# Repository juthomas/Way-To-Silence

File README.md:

# WAY TO SILENCE

## Goals
- Develop a module based on the ESP32, designed to read audio tracks stored on an SD card and to transmit them through a speaker output. Users should be able to adjust the parameters of these audio tracks, such as volume and balance, via an intuitive and easily accessible web interface. Furthermore, control over the tracks and playback settings via UDP signals is essential. This interface will provide users with the opportunity to customize their listening experience and adjust settings to their preferences. It will also ensure quick and efficient communication with the module through the UDP protocol. In addition, effective battery management is crucial to ensure the module's durability and optimal performance.

## 3D Render

## Schematics

- [Link to pdf](https://github.com/juthomas/Way-To-Silence/blob/main/Schematics%20PDF/Way%20to%20silence.pdf)

## Bill Of Materials

- [Link to IBOM](https://juthomas.github.io/Way-To-Silence/)
## Components
- [I2S Amplifier Module MAX98357A](https://www.lcsc.com/product-detail/Audio-Power-OpAmps_Analog-Devices-Inc-Maxim-Integrated-MAX98357AETE-T_C910544.html) € 0.7886

- [SD Card Connector](https://jlcpcb.com/partdetail/gswitch-GT_TF003_H018502/C5155564) € 0.1553

- [ESP32 4Mb Flash](https://www.lcsc.com/product-detail/WiFi-Modules_Espressif-Systems-ESP32-WROOM-32-N4_C82899.html) € 2.5764

- [ESP32 8Mb Flash](https://www.lcsc.com/product-detail/WiFi-Modules_Espressif-Systems-ESP32-WROOM-32-N8_C529582.html) € 2.9722

- [ESP32 16Mb Flash](https://lcsc.com/product-detail/WiFi-Modules_Espressif-Systems-ESP32-WROOM-32-N16_C529581.html) € 3.3920

- [CP2102](https://www.lcsc.com/product-detail/USB-ICs_SILICON-LABS-CP2102-GMR_C6568.html) € 2.0075

- [CH340C](https://www.lcsc.com/product-detail/USB-ICs_WCH-Jiangsu-Qin-Heng-CH340C_C84681.html) € 0.45

- [BMS SM5308](https://www.lcsc.com/product-detail/Battery-Management-ICs_HICHON-SM5308_C5345582.html) € 0.2758
- [USB C Connector](https://jlcpcb.com/partdetail/Dealon-USB_TYPE_C018/C2927038) $ 0.0479
- [3.3V Regulator](https://www.lcsc.com/product-detail/Linear-Voltage-Regulators-LDO_UMW-Youtai-Semiconductor-Co-Ltd-AMS1117-3-3_C347222.html) € 0.0398

- [Bornier 3.5mm](https://www.lcsc.com/product-detail/Screw-terminal_Ningbo-Xinlaiya-Elec-XY350V-3-5-2P_C784942.html) € 0.1065
- [2.2uH Inductance](https://www.lcsc.com/product-detail/Inductors-SMD_KOHERelec-MDA4020-2R2M_C2847469.html) € 0.7154
- [1uH Inductance](https://www.lcsc.com/product-detail/Inductors-SMD_KOHERelec-MDA4020-1R0M_C2847468.html#) € 0.7287
- [Battery Switch](https://jlcpcb.com/partdetail/XkbConnectivity-SS12D10L3/C319013) € 0.8814
- [Reset Button](https://jlcpcb.com/partdetail/Xunpu-TS_1088R02026/C455280) € 0.0448

- [4.7nF Capacitor](https://jlcpcb.com/partdetail/55004-0603B472K500NT/C53987) € 0.0025
- [4.7uF Capacitor](https://jlcpcb.com/partdetail/20375-CL10A475KO8NNNC/C19666) € 0.0095
- [10uF Capacitor](https://jlcpcb.com/partdetail/MurataElectronics-GRM188R60J106ME47D/C77041) € 0.0085	
- [22uF Capacitor](https://jlcpcb.com/partdetail/60514-CL10A226MQ8NRNC/C59461) € 0.0085
- [100nF Capacitor](https://jlcpcb.com/partdetail/Yageo-CC0603KRX7R9BB104/C14663) € 0.0022
- [220pF Capacitor](https://jlcpcb.com/partdetail/1955-CL10B221KB8NNNC/C1603) € 0.0055
- [0Ω Resistor](https://jlcpcb.com/partdetail/21903-0603WAF0000T5E/C21189) € 0.0011
- [100mΩ Resistor](https://jlcpcb.com/partdetail/112253-0603WAF100LT5E/C111027) € 0.0039
- [500mΩ Resistor](https://jlcpcb.com/partdetail/Fojan-FRL0603FR500TS/C2934253) € 0.0031
- [1Ω Resistor](https://jlcpcb.com/partdetail/25955-0603WAJ010JT5E/C25212) € 0.0009
- [1kΩ Resistor](https://jlcpcb.com/partdetail/21904-0603WAF1001T5E/C21190) € 0.0006

- [5.11kΩ Resistor](https://jlcpcb.com/partdetail/419038-TC0350B5111T5E/C425414) € 0.0167
- [10kΩ Resistor](https://jlcpcb.com/partdetail/26547-0603WAF1002T5E/C25804) € 0.0009
- [1MΩ Resistor](https://jlcpcb.com/partdetail/23662-0603WAF1004T5E/C22935) € 0.0011
- [Red LED](https://jlcpcb.com/partdetail/85432-NCD0603R1/C84263) € 0.0078
- [Yellow LED](https://jlcpcb.com/partdetail/85437-NCD0603Y1/C84268) € 0.0111
- [Ferrite Bead](https://jlcpcb.com/partdetail/373749-CBW160808U470T/C394474) € 0.0030
- [Transistor](https://jlcpcb.com/partdetail/Shikues-BC817/C475629) € 0.0150

## Tools used

- [KiCad](https://www.kicad.org/)
- [KiCad Fabrication Toolkit Plugin](https://github.com/bennymeg/JLC-Plugin-for-KiCad)
- [KiCad Interactive Html Bom Plugin](https://github.com/openscopeproject/InteractiveHtmlBom)
- [LCSC](https://www.lcsc.com/)
- [JCLPCB](https://jlcpcb.com/)

- [EasyEDA to KiCad](https://wokwi.com/tools/easyeda2kicad)

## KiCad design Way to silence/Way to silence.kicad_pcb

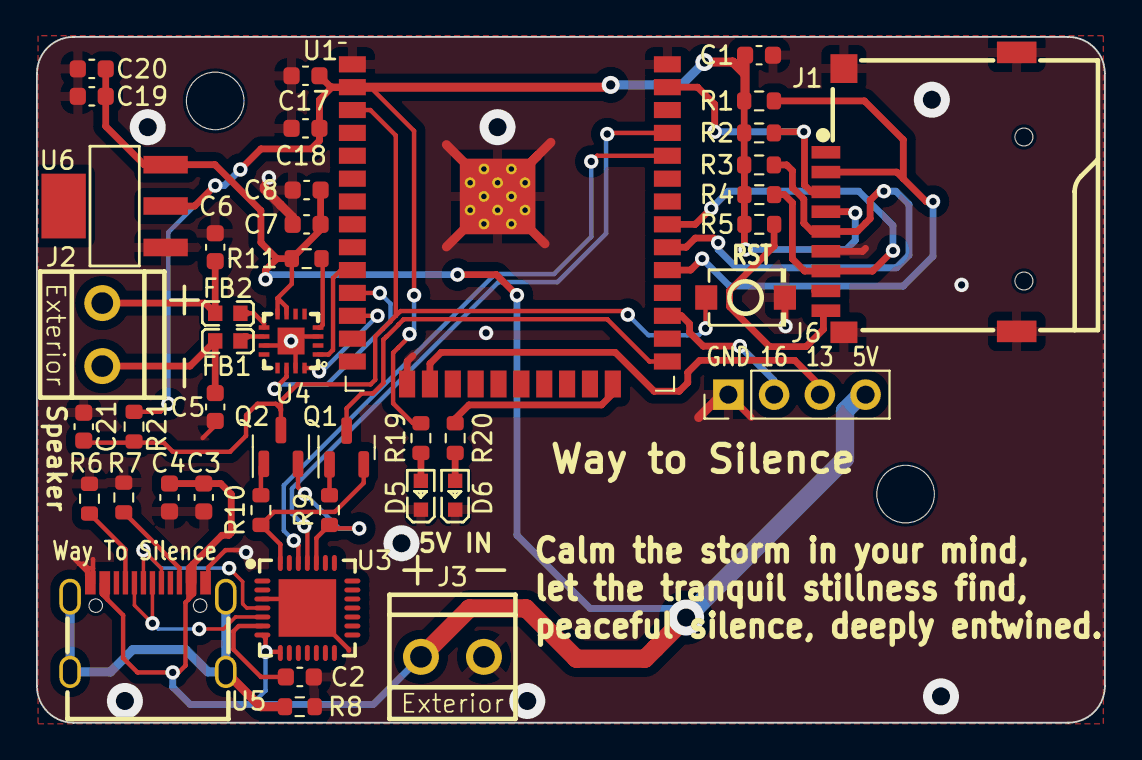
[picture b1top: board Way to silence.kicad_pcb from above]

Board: 2 copper layers, 59.3 x 38.1 mm, 45 parts (0 on the bottom side), 35 nets.

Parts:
C1, C2, C3, C7, C18, C19: 100nF; C_0603_1608Metric
C4: 4.7uF; C_0603_1608Metric
C5, C6: 220pF; C_0603_1608Metric
C8, C17, C20, C21: 10uF; C_0603_1608Metric
D5, D6: LED; LED_0603
FB1, FB2: FerriteBead; FB_0603
H1, H2: MountingHole; MountingHole_3.2mm_M3
J1: SD Card Connector; SD_Card_Connector
J2: Amplificator_Terminal; Screw_Terminal_3.5
J3: 5V_Terminal; Screw_Terminal_3.5
J6: Conn_01x04_Pin; PinHeader_1x04_P2.54mm_Vertical
Q1, Q2: BC817; SOT-23
R1, R2, R3, R4, R5, R9, R10, R21: 10K; R_0603_1608Metric
R6, R7: 5.11K; R_0603_1608Metric
R8, R11: 1M; R_0603_1608Metric
R19, R20: 1K; R_0603_1608Metric
SW3: SW_SPST
U1: ESP32-WROOM-32-N16; ESP32-WROOM-32
U3: CP2102-GMR; CP2102
U4: MAX98357AETE+T; MAX98357
U5: USB-TYPE-C-018; USB_C_Receptacle
U6: AMS1117CD-3.3

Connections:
+3.3V: C1.1, C17.2, C18.2, J1.4 (VDD), R1.1, R2.1, R3.1, R4.1, R5.1, R19.2, R21.1, U1.2 (VDD), U6.2 (VO)
+5V: C3.2, C4.2, C7.2, C8.2, C19.2, C20.2, J3.1, J6.4, R11.1, U3.7 (VREGIN), U3.8 (VBUS), U4.7 (VDD), U4.8 (VDD), U5.A4 (VBUS), U5.A9 (VBUS), U5.B4 (VBUS), U5.B9 (VBUS), U6.3 (VI)
/ESP_EN: C21.2, Q2.3 (C), R21.2, SW3.1 (A), U1.3 (EN)
/ESP_IO0: Q1.3 (C), U1.25 (IO0)
/ESP_IO2: R20.2, U1.24 (IO2)
/ESP_IO5: J1.2 (DAT3/CD), R1.2, U1.29 (IO5)
/ESP_IO13: J6.3, U1.16 (IO13)
/ESP_IO16: J6.2, U1.27 (IO16)
/ESP_IO18: J1.5 (CLK), R3.2, U1.30 (IO18)
/ESP_IO19: J1.7 (DAT0), R4.2, U1.31 (IO19)
/ESP_IO23: J1.3 (CMD), R2.2, U1.37 (IO23)
/ESP_IO25: U1.10 (IO25), U4.1 (DIN)
/ESP_IO26: U1.11 (IO26), U4.14 (LRCLK)
/ESP_IO27: U1.12 (IO27), U4.16 (BCLK)
/ESP_RX: U1.34 (RXD0/IO3), U3.26 (TXD)
/ESP_TX: U1.35 (TXD0/IO1), U3.25 (RXD)
/I2S Amp/SD: R11.2, U4.4 (SD_MODE)
/SD Card/Card Inserted: J1.CD (Card_Inserted), R5.2
/USB to Uart/DN: U3.5 (D-), U5.A7 (DN1), U5.B7 (DN2)
/USB to Uart/DP: U3.4 (D+), U5.A6 (DP1), U5.B6 (DP2)
/USB to Uart/SH: R8.1, U5.0 (SH), U5.1 (SH), U5.2 (SH), U5.3 (SH)
GND: C1.2, C2.1, C3.1, C4.1, C5.1, C6.1, C7.1, C8.1, C17.1, C18.1, C19.1, C20.1, C21.1, D5.1 (K), D6.1 (K), J1.6 (VSS), J1.G (SHIELD), J3.2, J6.1, R6.2, R7.1, R8.2, SW3.2 (B), U1.1 (GND), U1.15 (GND), U1.38 (GND), U1.39 (GND), U3.3 (GND), U3.29 (GND), U4.3 (GND), U4.11 (GND), U4.15 (GND), U4.17 (EP), U5.A1 (GND), U5.A12 (GND), U5.B1 (GND), U5.B12 (GND), U6.1 (GND)
unnamed: D5.2 (A), R19.1
unnamed: D6.2 (A), R20.1
unnamed: C6.2, FB2.2, J2.1
unnamed: C5.2, FB1.2, J2.2
unnamed: Q1.1 (B), R9.2
unnamed: Q1.2 (E), R10.1, U3.28 (~DTR)
unnamed: Q2.1 (B), R10.2
unnamed: Q2.2 (E), R9.1, U3.24 (~RTS)
unnamed: C2.2, U3.6 (VDD)
unnamed: FB1.1, U4.10 (OUTN)
unnamed: FB2.1, U4.9 (OUTP)
unnamed: R6.1, U5.A5 (CC1)
unnamed: R7.2, U5.B5 (CC2)

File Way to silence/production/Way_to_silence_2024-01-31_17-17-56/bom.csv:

Designator,Footprint,Quantity,Value,LCSC Part #
"C1, C18, C19, C2, C3, C7",0603,6,100nF,C14663
"C17, C20, C21, C8",0603,4,10uF,C77041
C4,0603,1,4.7uF,C19666
"C5, C6",0603,2,220pF,C1603
"D5, D6",LED_0603,2,LED,C84268
"FB1, FB2",FB_0603,2,FerriteBead,C394474
J1,SD_Card_Connector,1,SD Card Connector,C5155564
J2,Screw_Terminal_3.5,1,Amplificator_Terminal,C784942
J3,Screw_Terminal_3.5,1,5V_Terminal,C784942
J6,PinHeader_1x04_P2.54mm_Vertical,1,Conn_01x04_Pin,
"Q1, Q2",SOT-23,2,BC817,C475629
"R1, R10, R2, R21, R3, R4, R5, R9",0603,8,10K,C25804
"R11, R8",0603,2,1M,C22935
"R19, R20",0603,2,1K,C21190
"R6, R7",0603,2,5.11K,C425414
SW3,SW_SPST,1,SW_SPST,C455280
U1,ESP32-WROOM-32,1,ESP32-WROOM-32-N16,C529581
U3,CP2102,1,CP2102-GMR,C6568
U4,MAX98357,1,MAX98357AETE+T,C910544
U5,USB_C_Receptacle,1,USB-TYPE-C-018,C2927038
U6,AMS1117CD-3.3,1,AMS1117CD-3.3,C347222

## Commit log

2023-10-02 [ADD] SD Card Sheet
2023-10-02 [DRC] Working on SD Sheet
2023-10-02 [UDPT] Changed pulled down to pulled up
2023-10-02 [ADD] DataSheets
2023-10-02 [ADD] USB To Uart Sheet
2023-10-02 [ADD] USB C Connections
2023-10-02 [ADD] 3v3 Reg to Components Sourcing
2023-10-02 [ADD] 3v3 Reg to project
2023-10-03 [DRC] Working on USB to UART Sheet
2023-10-03 [ADD] I2S AMP Sheet
2023-10-03 [ADD] Screw Connector
2023-10-03 [DRC] I2S Amp seems Sheet ok
2023-10-03 [ADD] BMS Sheet
2023-10-04 [DRC] Working on BMS Sheet
2023-10-04 [ADD] Completed some connections in main sheet
2023-10-05 [ADD] 3v3 Reg
2023-10-06 [DRC] No errors
2023-10-06 [ADD] New reg footprint and datasheet
2023-10-06 [ADD] LSCS Parts and Footprints for BMS
2023-10-06 [ADD] References in readme
2023-10-06 [UPDT] Switch source
2023-10-06 [ADD] I2S Amp LSCS Refs
2023-10-06 [ADD] LCSC References
2023-10-06 [ADD] SD Card LCSC Refs
2023-10-06 [ADD] Inductor references
2023-10-06 [ADD] Footprints for connectors
2023-10-06 [ADD] Missing footprints
2023-10-06 [ADD] Beg of routing
2023-10-06 [ADD] i2S Module placed
2023-10-06 [ADD] Routing placement seems ok
2023-10-06 [ADD] Placement adjustements
2023-10-06 [ADD] 3d Models
2023-10-06 [ADD] Board Shape ok
2023-10-06 [ADD] Update for mounting holes
2023-10-09 [FIX] DRC and replacing button
2023-10-09 [ADD] Pin header for leds
2023-10-10 [ADD] Styles to shematics
2023-10-10 [ADD] Root page style
2023-10-10 [ADD] Shematics files settings
2023-10-10 [ERC] 1 Warning cleaned
2023-10-10 [UDPT] Leds colors
2023-10-10 [UDPT] Sheet name
2023-10-10 [UDPT] Text sizes in footprints
2023-10-10 [RTN] Routing in progress
2023-10-11 [RTN] Non gnd completed
2023-10-11 [UDPT] Page Settings
2023-10-11 [DRC] Seems ok
2023-10-11 [ADD] Back Silkscreen
2023-10-11 [ADD] Qr code & website
2023-10-12 [FIX] Error in shematics
2023-10-12 [FIX] LCSC Parts property
2023-10-12 [ADD] Terminals Rotations
2023-10-12 [ADD] U6 Q1 Q2 Rotations
2023-10-12 [ADD] ESP32 Position file
2023-10-12 [ADD] Better 3D models
2023-10-12 [DRC] No warnings, no errors
2023-10-12 [ADD] IBOM
2023-10-12 [UPDT] IBOM
2023-10-13 [ADD] 3D View + Schematics PDF
2023-10-13 [ADD] IBOM to docs
2023-10-13 [FIX] Rename for host file
2023-10-13 [ADD] IBOM link to readme
2023-10-13 [ADD] Image
2023-10-13 [UDPT] Image
2023-10-13 [ADD] Image to readme
2023-11-16 [UDPT] IBOM
2023-11-17 [ADD] First design fixes
2023-11-20 [ADD] Notes to update design
2023-11-20 [ADD] Notes to update design (RST problem)
2023-11-30 [UDPT] Schematics from testings
2023-11-30 [UDPT] Pcb from schematics
2023-11-30 [ADD] IO port
2023-11-30 [ADD] Retro-engineering BMS notes
2023-11-30 [UDPT] Schematics from retro-engineering
2023-12-13 [CLEAN] Remove retro-engineering drawing
2024-01-31 [ADD] No battery version
2024-01-31 [FIX] Miss spelling
2024-01-31 [UDPT] Image for no battery version
